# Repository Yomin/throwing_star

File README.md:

# Throwing Star LAN Tap

Board for Michael Ossmanns famous Throwing Star ([Great Scott Gadgets](http://greatscottgadgets.com/throwingstar))

## License

GPLv2

## Parts

qty|name
---|---
4|RJ45 connectors
2|220pF capacitors

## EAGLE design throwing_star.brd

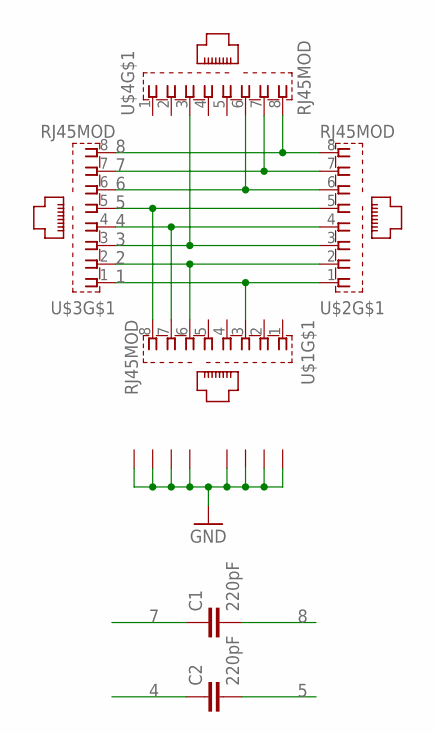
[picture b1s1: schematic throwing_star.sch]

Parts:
C1, C2: 220pF; C050-024X044
U$1, U$2, U$3, U$4: RJ45MOD

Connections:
1: U$1.3, U$2.1, U$3.1
2: U$1.6, U$2.2, U$3.2
3: U$2.3, U$3.3, U$4.3
4: C2.1, U$1.7, U$2.4, U$3.4
5: C2.2, U$1.8, U$2.5, U$3.5
6: U$2.6, U$3.6, U$4.6
7: C1.1, U$2.7, U$3.7, U$4.7
8: C1.2, U$2.8, U$3.8, U$4.8
GND: U$1.G3 (1), U$1.G4 (1), U$2.G3 (1), U$2.G4 (1), U$3.G3 (1), U$3.G4 (1), U$4.G3 (1), U$4.G4 (1)

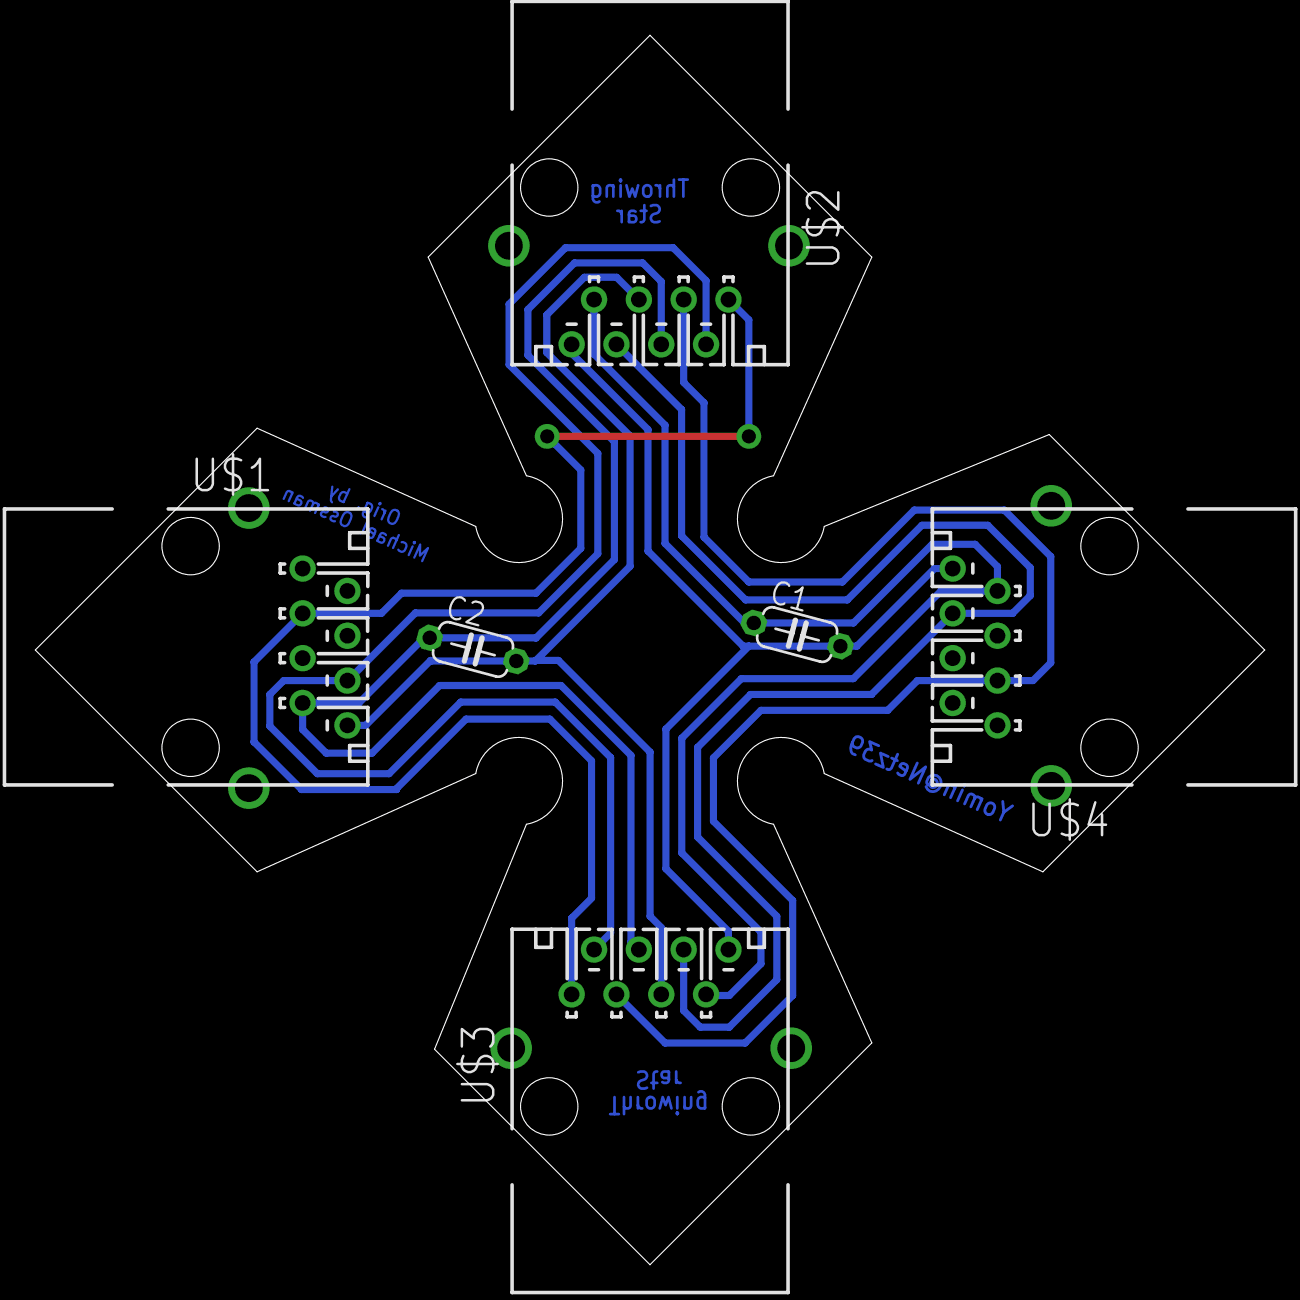
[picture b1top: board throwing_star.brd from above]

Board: 2 copper layers, 69.7 x 69.7 mm, 6 parts (0 on the bottom side), 9 nets.

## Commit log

2013-03-08 initial version
2013-03-09 adjust text, add logo
2013-03-09 condense to ~50x50mm
2013-03-16 change rj45 jacks and reroute
